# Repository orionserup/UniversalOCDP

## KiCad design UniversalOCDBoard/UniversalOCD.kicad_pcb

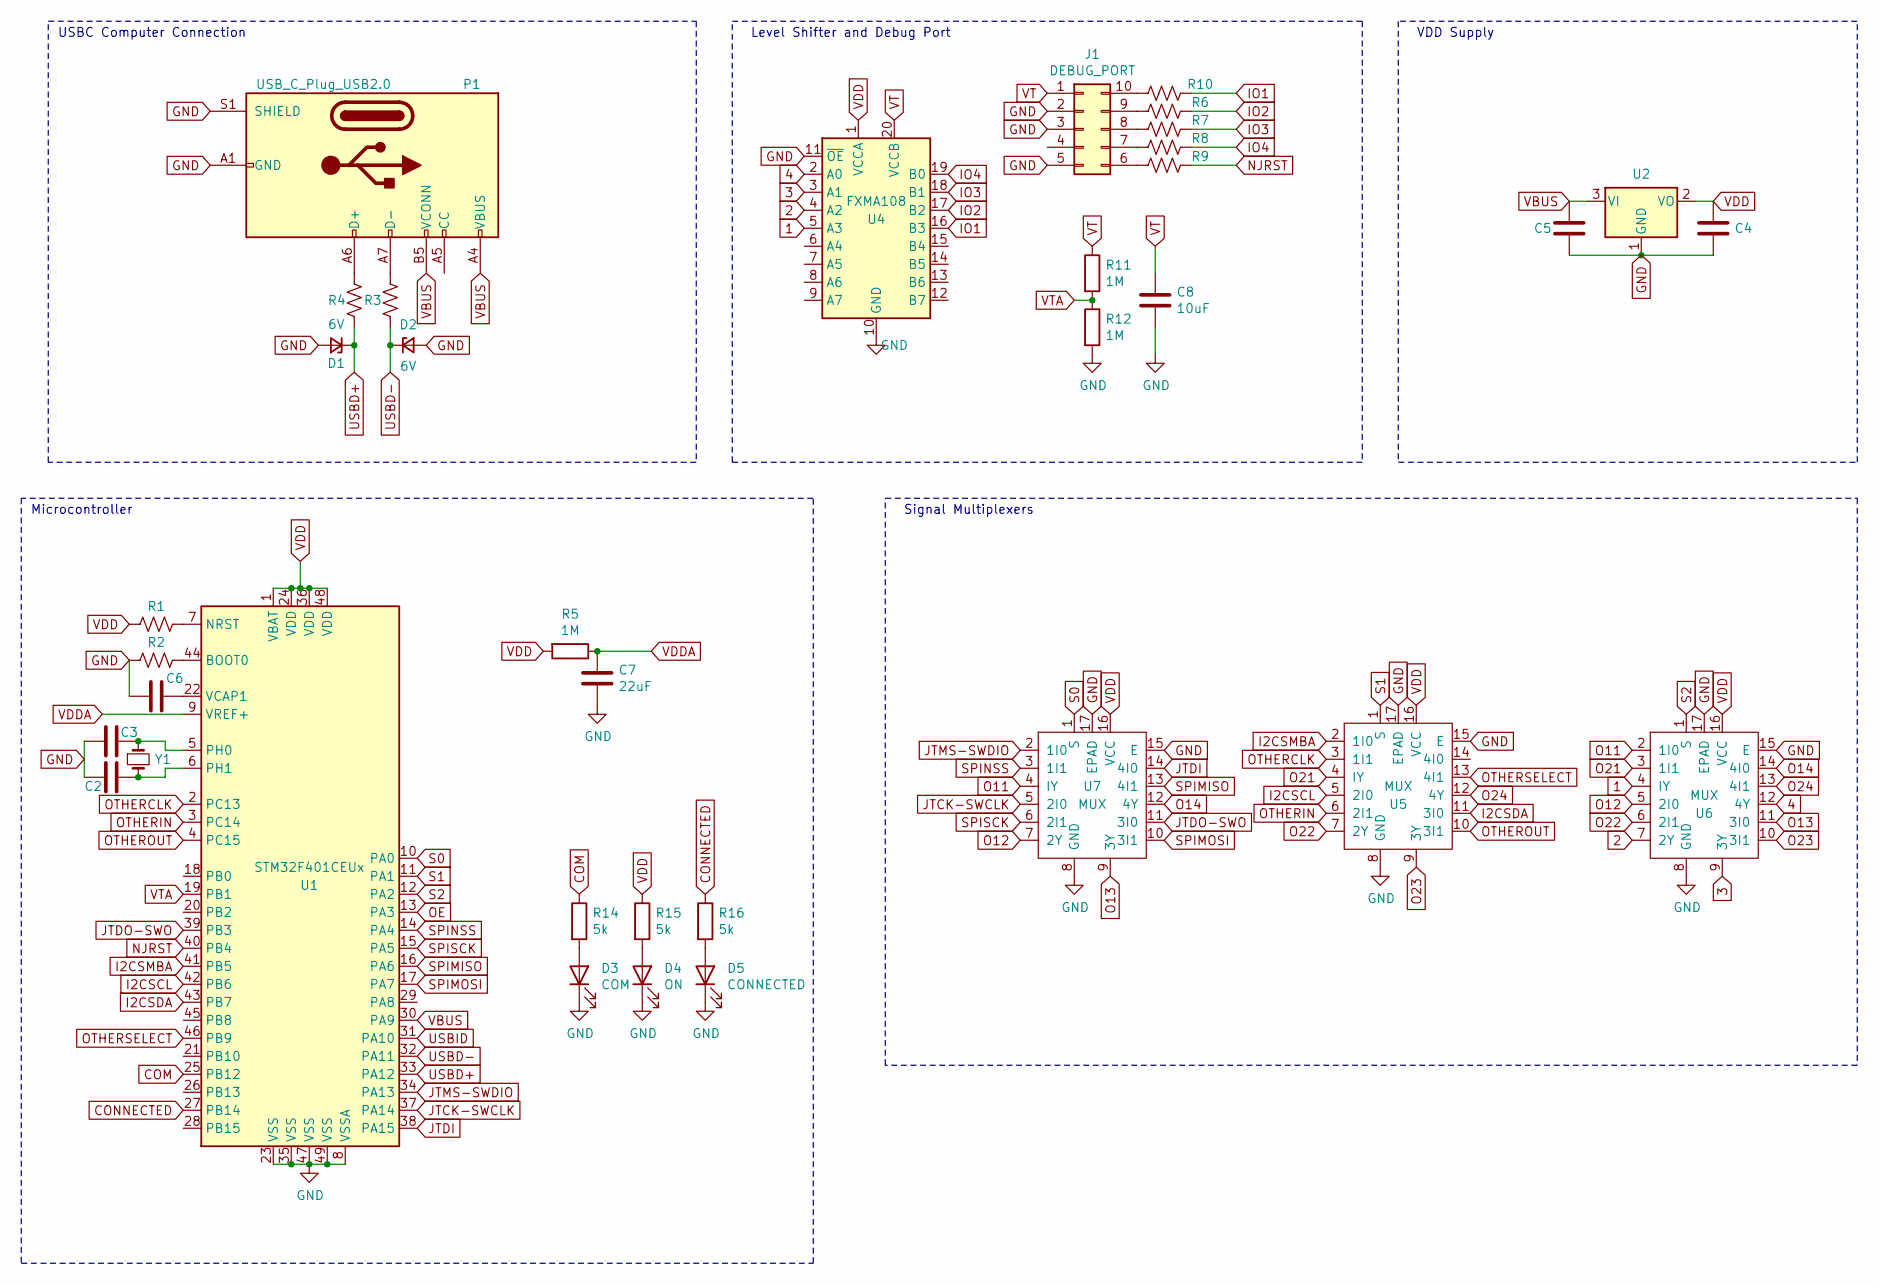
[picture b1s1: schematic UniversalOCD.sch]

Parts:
C2, C3: 22pF; C_0603_1608Metric
C4, C5: 10uF; C_0805_2012Metric
C6: 4.7uF; C_1206_3216Metric
C7: 22uF; C_1206_3216Metric
C8: 10uF; C_1206_3216Metric
D1, D2: 6V; D_0805_2012Metric
D3: COM; LED_0805_2012Metric_Pad1.15x1.40mm_HandSolder
D4: ON; LED_0805_2012Metric_Pad1.15x1.40mm_HandSolder
D5: CONNECTED; LED_0805_2012Metric_Pad1.15x1.40mm_HandSolder
J1: DEBUG_PORT; DEBUG
P1: USB_C_Plug_USB2.0; USB_C_Receptacle_HRO_TYPE-C-31-M-12
R1, R2: 10k; R_0805_2012Metric
R3, R4: 22R; R_0805_2012Metric_Pad1.20x1.40mm_HandSolder
R5: 1M; R_0805_2012Metric_Pad1.20x1.40mm_HandSolder
R6, R7, R8, R9, R10: 100; R_0603_1608Metric
R11, R12: 1M; R_0805_2012Metric
R14, R15, R16: 5k; R_0805_2012Metric
U1: STM32F401CEUx; QFN-48-1EP_7x7mm_P0.5mm_EP5.6x5.6mm
U2: AP2127N-3.0; SOT-23
U4: FXMA108; WQFN-20-1EP_2.5x4.5mm_P0.5mm_EP1x2.9mm
U5, U6, U7: MUX; DVQFN-16
Y1: Crystal_Small; Crystal_SMD_TXC_9HT11-2Pin_2.0x1.2mm

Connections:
1: U4.5 (A3), U6.4 (IY)
2: U4.4 (A2), U6.7 (2Y)
3: U4.3 (A1), U6.9 (3Y)
4: U4.2 (A0), U6.12 (4Y)
COM: R14.1, U1.25 (PB12)
CONNECTED: R16.1, U1.27 (PB14)
GND: C2.2, C3.2, C4.2, C5.2, C6.2, C7.2, C8.2, D1.2 (A), D2.2 (A), D3.1 (K), D4.1 (K), D5.1 (K), J1.2, J1.3, J1.5, P1.A1 (GND), P1.A12 (GND), P1.B1 (GND), P1.B12 (GND), P1.S1 (SHIELD), R2.2, R12.2, U1.8 (VSSA), U1.23 (VSS), U1.35 (VSS), U1.47 (VSS), U1.49 (VSS), U2.1 (GND), U4.10 (GND), U4.11 (~OE), U5.8 (GND), U5.15 (E), U5.17 (EPAD), U6.8 (GND), U6.15 (E), U6.17 (EPAD), U7.8 (GND), U7.15 (E), U7.17 (EPAD)
I2CSCL: U1.42 (PB6), U5.5 (2I0)
I2CSDA: U1.43 (PB7), U5.11 (3I0)
I2CSMBA: U1.41 (PB5), U5.2 (1I0)
IO1: R10.1, U4.16 (B3)
IO2: R6.1, U4.17 (B2)
IO3: R7.1, U4.18 (B1)
IO4: R8.1, U4.19 (B0)
JTCK-SWCLK: U1.37 (PA14), U7.5 (2I0)
JTDI: U1.38 (PA15), U7.14 (4I0)
JTDO-SWO: U1.39 (PB3), U7.11 (3I0)
JTMS-SWDIO: U1.34 (PA13), U7.2 (1I0)
NJRST: R9.1, U1.40 (PB4)
unnamed: C2.1, U1.6 (PH1), Y1.2
unnamed: C3.1, U1.5 (PH0), Y1.1
unnamed: C6.1, U1.22 (VCAP1)
unnamed: D3.2 (A), R14.2
unnamed: D4.2 (A), R15.2
unnamed: D5.2 (A), R16.2
unnamed: J1.6, R9.2
unnamed: J1.7, R8.2
unnamed: J1.8, R7.2
unnamed: J1.9, R6.2
unnamed: J1.10, R10.2
unnamed: P1.A6 (D+), R4.1
unnamed: P1.A7 (D-), R3.1
unnamed: R1.1, U1.7 (NRST)
unnamed: R2.1, U1.44 (BOOT0)
O11: U6.2 (1I0), U7.4 (IY)
O12: U6.5 (2I0), U7.7 (2Y)
O13: U6.11 (3I0), U7.9 (3Y)
O14: U6.14 (4I0), U7.12 (4Y)
O21: U5.4 (IY), U6.3 (1I1)
O22: U5.7 (2Y), U6.6 (2I1)
O23: U5.9 (3Y), U6.10 (3I1)
O24: U5.12 (4Y), U6.13 (4I1)
OE: U1.13 (PA3)
OTHERCLK: U1.2 (PC13), U5.3 (1I1)
OTHERIN: U1.3 (PC14), U5.6 (2I1)
OTHEROUT: U1.4 (PC15), U5.10 (3I1)
OTHERSELECT: U1.46 (PB9), U5.13 (4I1)
S0: U1.10 (PA0), U7.1 (S)
S1: U1.11 (PA1), U5.1 (S)
S2: U1.12 (PA2), U6.1 (S)
SPIMISO: U1.16 (PA6), U7.13 (4I1)
SPIMOSI: U1.17 (PA7), U7.10 (3I1)
SPINSS: U1.14 (PA4), U7.3 (1I1)
SPISCK: U1.15 (PA5), U7.6 (2I1)
USBD+: D1.1 (K), R4.2, U1.33 (PA12)
USBD-: D2.1 (K), R3.2, U1.32 (PA11)
USBID: U1.31 (PA10)
VBUS: C5.1, P1.A4 (VBUS), P1.A9 (VBUS), P1.B4 (VBUS), P1.B5 (VCONN), P1.B9 (VBUS), U1.30 (PA9), U2.3 (VI)
VDD: C4.1, R1.2, R5.2, R15.1, U1.1 (VBAT), U1.24 (VDD), U1.36 (VDD), U1.48 (VDD), U2.2 (VO), U4.1 (VCCA), U5.16 (VCC), U6.16 (VCC), U7.16 (VCC)
VDDA: C7.1, R5.1, U1.9 (VREF+)
VT: C8.1, J1.1, R11.1, U4.20 (VCCB)
VTA: R11.2, R12.1, U1.19 (PB1)

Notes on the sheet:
Microcontroller
USBC Computer Connection
Level Shifter and Debug Port
Signal Multiplexers
VDD Supply

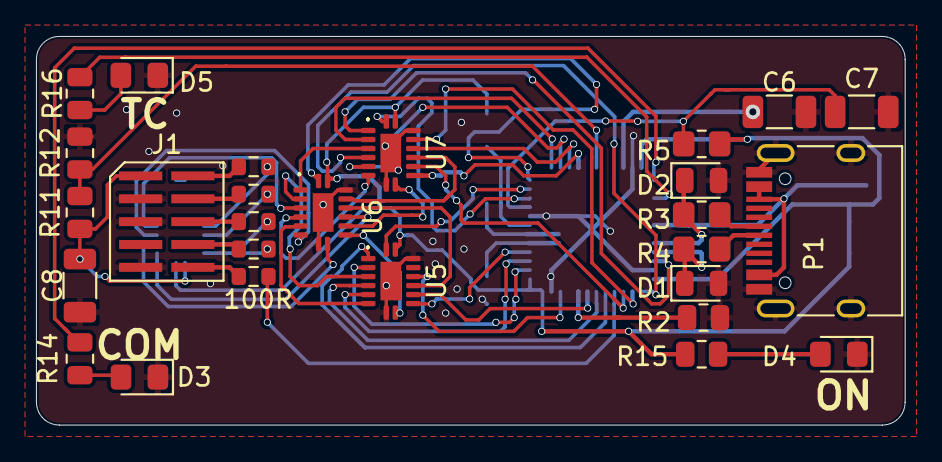
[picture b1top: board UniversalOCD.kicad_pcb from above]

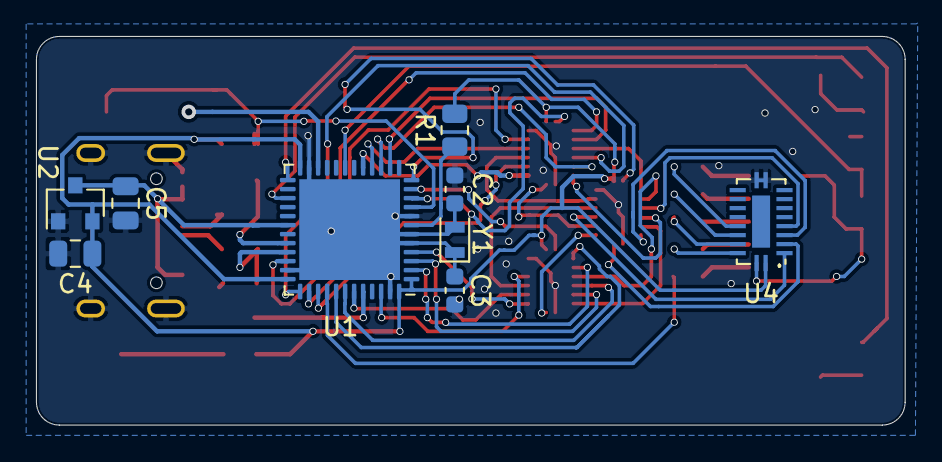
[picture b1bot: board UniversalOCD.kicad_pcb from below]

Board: 2 copper layers, 48.3 x 21.6 mm, 37 parts (9 on the bottom side), 60 nets.

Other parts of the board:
MUX: DVQFN-16

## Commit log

2020-10-27 board
